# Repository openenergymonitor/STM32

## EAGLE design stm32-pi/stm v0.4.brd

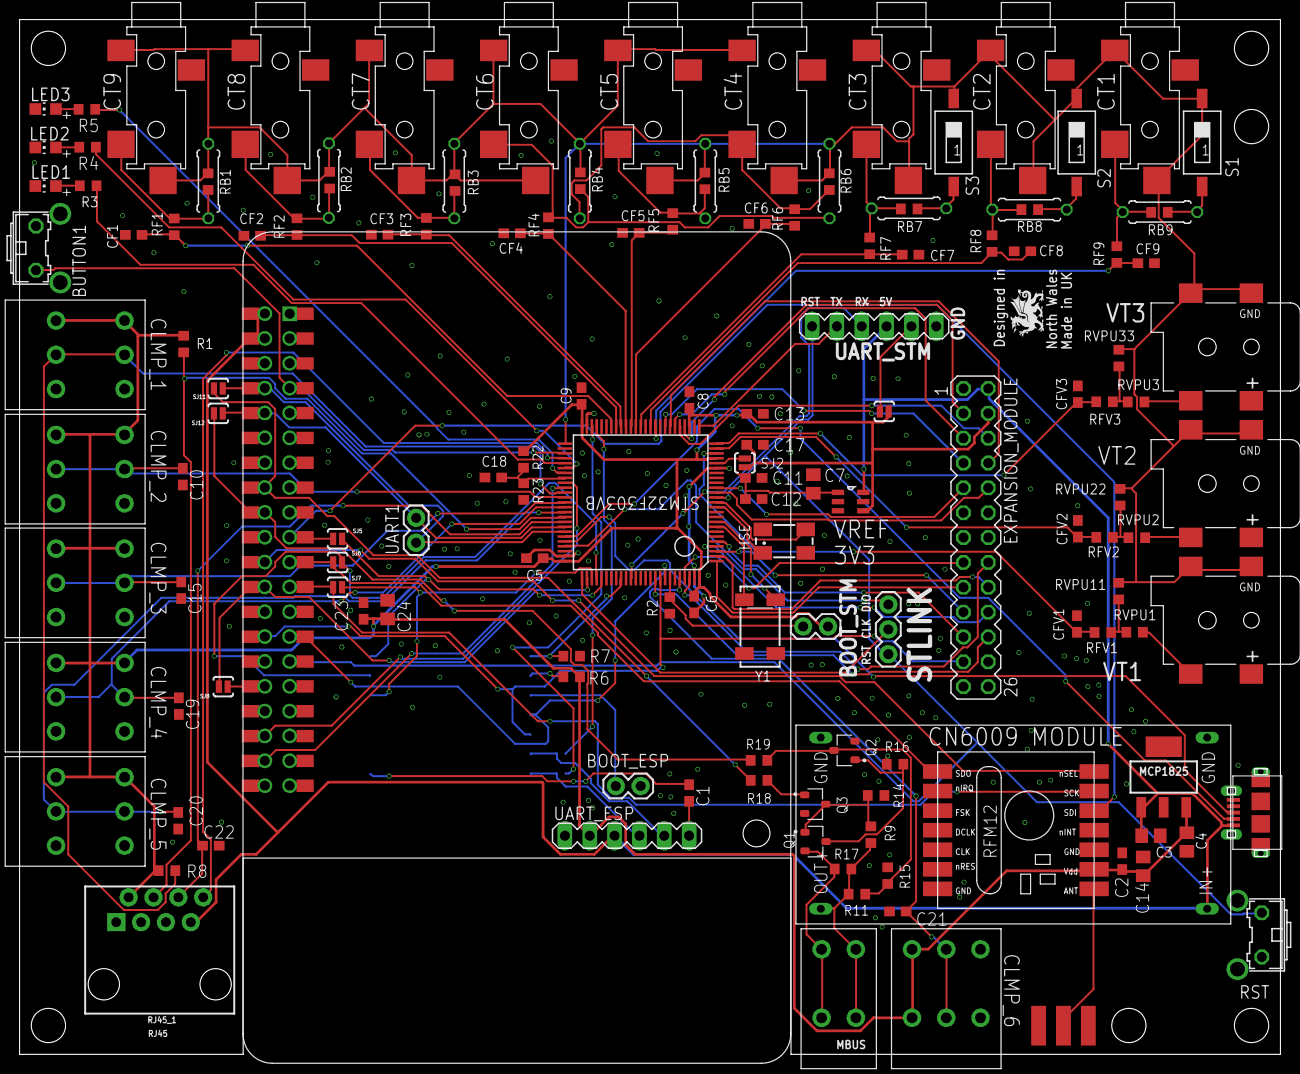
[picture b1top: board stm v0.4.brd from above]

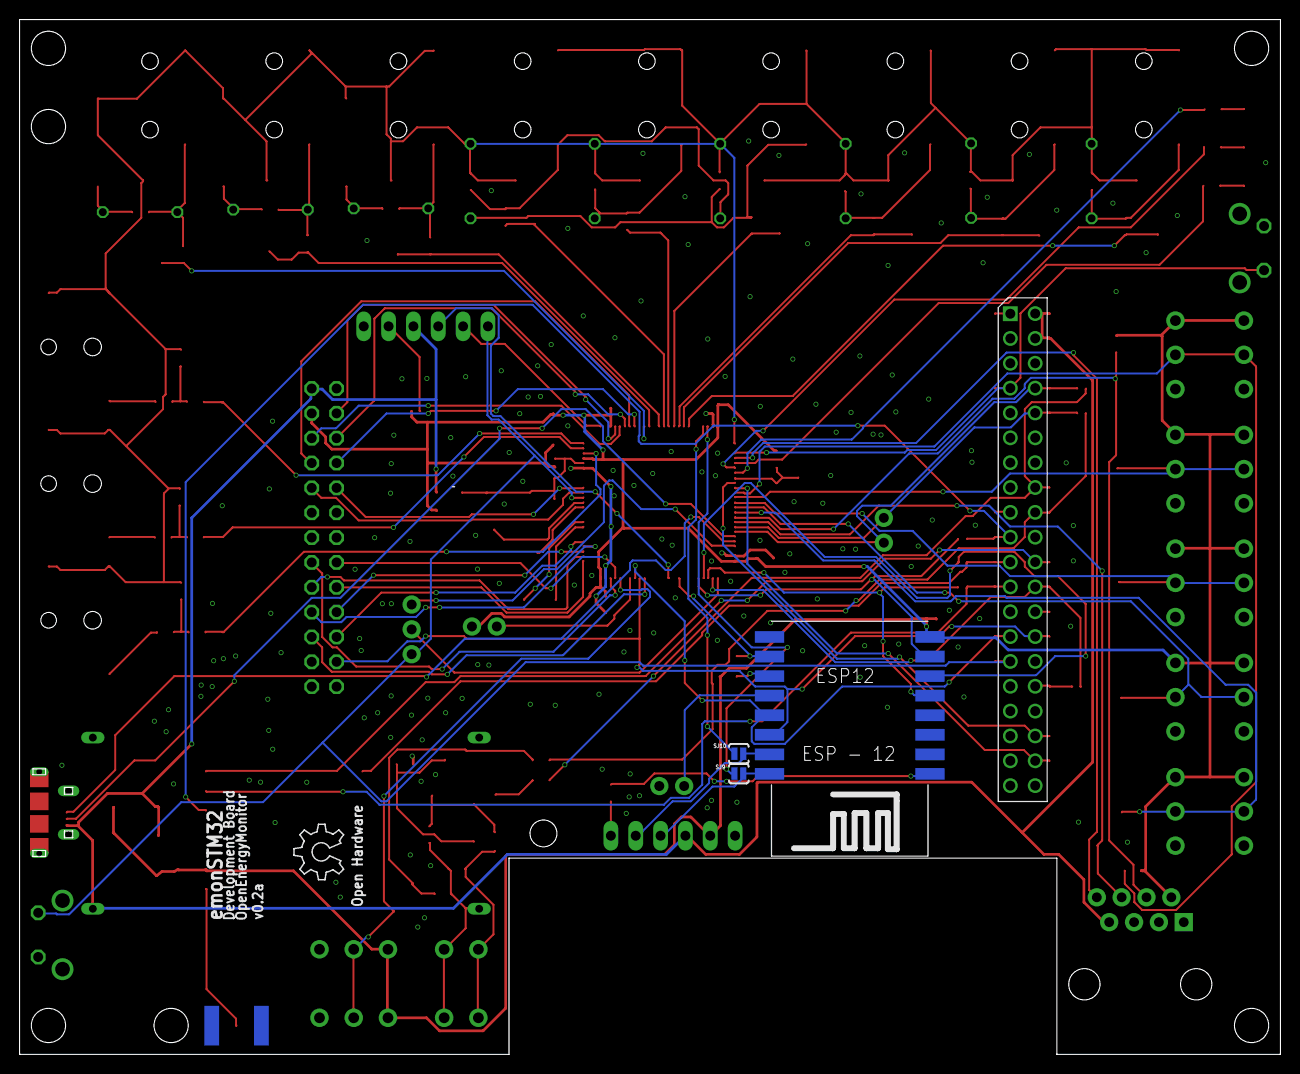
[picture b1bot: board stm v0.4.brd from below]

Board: 2 copper layers, 128.9 x 105.8 mm, 149 parts (4 on the bottom side), 116 nets.

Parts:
2POLE_MBUS: OMNIMATE_LSF_2
3POLE_1, 3POLE_2, 3POLE_3, 3POLE_4, 3POLE_5, 3POLE_6: OMNIMATE_LSF_3
BOOT_ESP: 1X02
BOOT_STM: 1X02
BUTTON1: B3F-31XX
C1, C2, C5, C6, C8, C9, C10, C15, C19, C20, C21, C22, C23: 100nF; C0603
C3, C4: 4.7uF; C0805
C7, C14: 1uF; C0805
C11, C13: 10nF; C0603
C12, C17: 1uF; C0603
C18: 10uF; C0603
C24: 47uF; C0805
CF1, CF2, CF3, CF4, CF5, CF6, CF7, CF8, CF9: 100nF; C0603
CFV1, CFV2, CFV3: 100nF; C0603
CT1, CT2, CT3, CT4, CT5, CT6, CT7, CT8, CT9: STEREO_SMD; STEREO_SMT
ESP12: ESP12-SMD
EXPANSION_MODULE: MA13-2
HSE: 8MHZ ~15pFmax; CTS406
J$1: SMA_EDGE; SMA-EDGE
LED1, LED2, LED3: Red 1.85V; CHIP-LED0805
LOGO1: OSHW_LOGO_6MILX0200-NT; OSHW_6X200_NOTEXT
MCP1825: MCP1825SOT-223-3; SOT-223
PCB2: RPI3YA; RPI3MIRROR2
Q1: MMBT3906; SOT23
Q2, Q3: MMBT3904; SOT23
R1, R8: 4.7k; R0603
R2, R6, R7, R22, R23: 10k; R0603
R3, R4, R5: 220R; R0603
R9: 39K; R0603
R11: 33K; R0603
R14: 22K; R0603
R15: 3k3; R0603
R16: 82R; R0603
R17: 220K; R0603
R18, R19: 1K; R0603
RB1, RB2, RB3, RB4, RB5, RB6, RB7, RB8, RB9: 22r; R0603
RB10, RB11, RB12, RB13, RB14, RB15, RB16, RB17, RB18: 22r; 0207/7
RF1, RF2, RF3, RF4, RF5, RF6, RF7, RF8, RF9: 330R; R0603
RFM69HCW: RFM12_SMDSMD; RFM12
RFV1, RFV2, RFV3: 330R; R0603
RJ45_1: RJ45; RJ45-8
RST: B3F-31XX
RVPU1, RVPU2, RVPU3: 120k; R0603
RVPU11, RVPU22, RVPU33: 10k; R0603
S1, S2, S3: SWS001; SMS-001
SJ1, SJ2, SJ5, SJ6, SJ7, SJ8, SJ9, SJ10, SJ11, SJ12: SOLDERJUMPERNO; SJ_2S-NO
STLINK: 1X03
STM32F303VB: STM32F303XB; TQFP100
U$2: BOOST_MODULE; BOOST
UART1: 1X02
UART_ESP: MA06-1
UART_STM: MA06-1
USB_CONN: MICRO-USB-RECEPTACLE47589-0001; 47589-0001
VREF_3V3: MCP1501T-33E; SOT95P280X145-6N
VT1, VT2, VT3: 2.1MMJACKSMT; DCJACK_2MM_SMT
Y1: 32.768kHz; CRYSTAL_8X3.8

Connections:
24V: 2POLE_MBUS.P$3, 2POLE_MBUS.P$4, R9.2, R11.2, R17.2, U$2.OUT+
+3V3: 3POLE_1.P$1, 3POLE_1.P$2, 3POLE_2.P$1, 3POLE_2.P$2, 3POLE_3.P$1, 3POLE_3.P$2, 3POLE_4.P$1, 3POLE_4.P$2, 3POLE_5.P$1, 3POLE_5.P$2, 3POLE_6.P$1, 3POLE_6.P$2, BOOT_STM.2, C2.1, C4.2, C5.2, C6.2, C8.2, C9.2, C13.1, C14.1, C17.1, C23.1, C24.1, ESP12.VCC, EXPANSION_MODULE.4, MCP1825.3, R1.2, R6.2, R8.2, R22.2, RFM69HCW.9, RJ45_1.2, SJ1.2, SJ2.1, STM32F303VB.22, STM32F303VB.28, STM32F303VB.50, STM32F303VB.75, STM32F303VB.100, UART_ESP.2, VREF_3V3.4
+3V3_ADC: C7.1, C11.1, C12.1, SJ2.2, STM32F303VB.21, VREF_3V3.1
+5V: C3.2, EXPANSION_MODULE.2, MCP1825.1, PCB2.P$2, PCB2.P$4, PCB2.P$42, PCB2.P$44, RJ45_1.7, U$2.IN+, UART_ESP.3, UART_STM.3, USB_CONN.1, VREF_3V3.6
AC1: RVPU1.2, VT1.PWR2
AC2: RVPU2.2, VT2.PWR2
AC3: RVPU3.1, VT3.PWR2
ADC0: RFV3.1, RVPU3.2, RVPU33.1
ADC_RJ45IN: RJ45_1.8, STM32F303VB.54
ANT: J$1.SIG, RFM69HCW.8
BIAS: CT1.P$1, CT1.P$4, CT2.P$1, CT2.P$4, CT3.P$1, CT3.P$4, CT4.P$1, CT4.P$4, CT5.P$1, CT5.P$4, CT6.P$1, CT6.P$4, CT7.P$1, CT7.P$4, CT8.P$1, CT8.P$4, CT9.P$1, CT9.P$4, RB1.2, RB2.2, RB3.2, RB4.2, RB5.2, RB6.2, RB10.2, RB11.2, RB12.2, RB13.2, RB14.2, RB15.2, RVPU11.2, RVPU22.2, RVPU33.2, S1.2, S2.2, S3.2, STM32F303VB.51, VT1.GND, VT1.GNDBREAK, VT2.GND, VT2.GNDBREAK, VT3.GND, VT3.GNDBREAK
BIAS_IN: C18.2, R22.1, R23.2, STM32F303VB.58
BOOT0: BOOT_STM.1, R2.1, STM32F303VB.94
BUTTON1: BUTTON1.2, PCB2.P$7, PCB2.P$47, STM32F303VB.53
CS_RFM69: PCB2.P$22, PCB2.P$62, RFM69HCW.14
CT1: CF1.2, RF1.2, STM32F303VB.44
CT1_EX: EXPANSION_MODULE.3, STM32F303VB.29
CT2: CF2.2, RF2.2, STM32F303VB.43
CT2_EX: EXPANSION_MODULE.6, STM32F303VB.30
CT3: CF3.2, RF3.2, STM32F303VB.42
CT3_EX: EXPANSION_MODULE.5, STM32F303VB.31
CT4: CF4.2, RF4.2, STM32F303VB.41
CT4_EX: EXPANSION_MODULE.8, STM32F303VB.32
CT5: CF5.2, RF5.2, STM32F303VB.40
CT5_EX: EXPANSION_MODULE.7, STM32F303VB.33
CT6: CF6.2, RF6.2, STM32F303VB.39
CT6_EX: EXPANSION_MODULE.10, STM32F303VB.15
CT7: CF7.2, RF7.2, STM32F303VB.38
CT7_EX: EXPANSION_MODULE.9, STM32F303VB.16
CT8: CF8.2, RF8.2, STM32F303VB.36
CT9: CF9.2, RF9.2, STM32F303VB.35
D+: STM32F303VB.71, USB_CONN.3
D-: STM32F303VB.70, USB_CONN.2
DS18B20_2: 3POLE_1.P$3, 3POLE_1.P$4, R8.1, STM32F303VB.61
DS18B20_RJ45: R1.1, RJ45_1.4, STM32F303VB.66
GND: 3POLE_1.P$5, 3POLE_1.P$6, 3POLE_2.P$5, 3POLE_2.P$6, 3POLE_3.P$5, 3POLE_3.P$6, 3POLE_4.P$5, 3POLE_4.P$6, 3POLE_5.P$5, 3POLE_5.P$6, 3POLE_6.P$5, 3POLE_6.P$6, BOOT_ESP.2, BUTTON1.1, C2.2, C3.1, C4.1, C5.1, C6.1, C7.2, C8.1, C9.1, C10.2, C11.2, C12.2, C13.2, C14.2, C15.2, C17.2, C18.1, C19.2, C20.2, C21.2, C22.2, C23.2, C24.2, CF1.1, CF2.1, CF3.1, CF4.1, CF5.1, CF6.1, CF7.1, CF8.1, CF9.1, CFV1.1, CFV2.1, CFV3.1, ESP12.GND, EXPANSION_MODULE.1, EXPANSION_MODULE.14, EXPANSION_MODULE.26, J$1.GND@0, J$1.GND@1, J$1.GND@2, J$1.GND@3, LED1.C, LED2.C, LED3.C, MCP1825.2, MCP1825.4, PCB2.P$6, PCB2.P$9, PCB2.P$14, PCB2.P$20, PCB2.P$25, PCB2.P$30, PCB2.P$34, PCB2.P$39, PCB2.P$46, PCB2.P$49, PCB2.P$54, PCB2.P$60, PCB2.P$65, PCB2.P$70, PCB2.P$74, PCB2.P$79, Q2.2, Q3.2, R2.2, R7.2, R14.1, R15.1, R16.1, R23.1, RFM69HCW.7, RFM69HCW.10, RJ45_1.1, RJ45_1.3, RJ45_1.5, RST.1, STM32F303VB.20, STM32F303VB.49, STM32F303VB.74, STM32F303VB.99, U$2.P$1, U$2.P$2, UART_ESP.1, UART_STM.1, USB_CONN.5, USB_CONN.CASING1, USB_CONN.CASING2, USB_CONN.CASING3, USB_CONN.CASING4, VREF_3V3.2, VREF_3V3.3, VREF_3V3.5
HSE_IN: HSE.1, STM32F303VB.12
HSE_OUT: HSE.3, STM32F303VB.13
IO1_EX: EXPANSION_MODULE.15, STM32F303VB.97
IO2_EX: EXPANSION_MODULE.16, STM32F303VB.98
IO3_EX: EXPANSION_MODULE.17, STM32F303VB.1
IO4_EX: EXPANSION_MODULE.18, STM32F303VB.2
IO5_EX: EXPANSION_MODULE.19, STM32F303VB.3
IO6_EX: EXPANSION_MODULE.20, STM32F303VB.4
IO7_EX: EXPANSION_MODULE.21, STM32F303VB.5
IO8_EX: EXPANSION_MODULE.22, STM32F303VB.91
LED1: R3.2, STM32F303VB.55
LED2: R4.2, STM32F303VB.56
LED3: R5.2, STM32F303VB.57
MBUS_RX: PCB2.P$16, PCB2.P$56, R18.2, SJ11.2
MBUS_TX: PCB2.P$18, PCB2.P$58, R19.2, SJ12.2
MISO: PCB2.P$21, PCB2.P$61, RFM69HCW.1, SJ6.2
MOSI: PCB2.P$19, PCB2.P$59, RFM69HCW.12, SJ5.2
unnamed: SJ1.1, UART_STM.2
unnamed: CT9.P$2, RB1.1, RB10.1, RF1.1
unnamed: LED2.A, R4.1
unnamed: LED3.A, R5.1
unnamed: BOOT_ESP.1, ESP12.GPIO0
unnamed: CT8.P$2, RB2.1, RB11.1, RF2.1
unnamed: CT7.P$2, RB3.1, RB12.1, RF3.1
unnamed: ESP12.GPIO2, R6.1
unnamed: PCB2.P$26, PCB2.P$66
unnamed: PCB2.P$32, PCB2.P$72, SJ8.1
unnamed: PCB2.P$1, PCB2.P$41
unnamed: PCB2.P$17, PCB2.P$57
unnamed: RB9.2, RB18.2, S1.1
unnamed: RB8.2, RB17.2, S2.1
unnamed: RB7.2, RB16.2, S3.1
unnamed: 2POLE_MBUS.P$1, 2POLE_MBUS.P$2, Q1.2, R17.1
unnamed: Q1.3, Q2.1, R16.2
unnamed: Q1.1, Q3.3, R9.1, R14.2
unnamed: Q2.3, R11.1, R15.2, R19.1
unnamed: Q3.1, R18.1
unnamed: RFV2.1, RVPU2.1, RVPU22.1
unnamed: RFV1.1, RVPU1.1, RVPU11.1
unnamed: CT6.P$2, RB4.1, RB15.1, RF4.1
unnamed: CT5.P$2, RB5.1, RB14.1, RF5.1
unnamed: CT4.P$2, RB6.1, RB13.1, RF6.1
unnamed: LED1.A, R3.1
unnamed: CT3.P$2, RB7.1, RB16.1, RF7.1
unnamed: CT2.P$2, RB8.1, RB17.1, RF8.1
unnamed: CT1.P$2, RB9.1, RB18.1, RF9.1
NRST: PCB2.P$29, PCB2.P$69, RST.2, STLINK.3, STM32F303VB.14, UART_STM.6
PC14: STM32F303VB.8, Y1.P$1
PC15: STM32F303VB.9, Y1.P$4
PULSE1_RJ45: C22.1, RJ45_1.6, STM32F303VB.67
PULSE2: 3POLE_5.P$3, 3POLE_5.P$4, C20.1, STM32F303VB.65
PUSHIN_1: 3POLE_6.P$3, 3POLE_6.P$4, C21.1, STM32F303VB.96
PUSHIN_2: 3POLE_2.P$3, 3POLE_2.P$4, C10.1, STM32F303VB.62
PUSHIN_3: 3POLE_3.P$3, 3POLE_3.P$4, C15.1, STM32F303VB.63
PUSHIN_4: 3POLE_4.P$3, 3POLE_4.P$4, C19.1, STM32F303VB.64
RPI_GPIO16: PCB2.P$36, PCB2.P$76, STM32F303VB.59
RPI_GPIO20: PCB2.P$38, PCB2.P$78, STM32F303VB.60
RST_ESP_1: C1.2, UART_ESP.6
RST_ESP_2: C1.1, ESP12.RESET
SCK: ESP12.GPIO5, EXPANSION_MODULE.23, PCB2.P$28, PCB2.P$68, STM32F303VB.92
SDA: ESP12.GPIO4, PCB2.P$27, PCB2.P$67, STM32F303VB.93
SPI3_CLK: ESP12.GPIO14, SJ7.1, STM32F303VB.78
SPI3_CS: PCB2.P$24, PCB2.P$64, SJ8.2, STM32F303VB.77
SPI3_CS_ESP: ESP12.GPIO15, R7.1, STM32F303VB.84
SPI3_MISO: ESP12.GPIO12, SJ6.1, STM32F303VB.79
SPI3_MOSI: ESP12.GPIO13, SJ5.1, STM32F303VB.80
SPI_CLK: PCB2.P$23, PCB2.P$63, RFM69HCW.13, SJ7.2
SWCLK: STLINK.2, STM32F303VB.76
SWDIO: STLINK.1, STM32F303VB.72
UART1_RX: PCB2.P$8, PCB2.P$48, SJ11.1, STM32F303VB.69, UART1.1
UART1_TX: PCB2.P$10, PCB2.P$50, SJ12.1, STM32F303VB.68, UART1.2
UART_RX: STM32F303VB.86, UART_STM.4
UART_RX_ESP: ESP12.TXD0, SJ9.2, UART_ESP.4
UART_TX: STM32F303VB.26, UART_STM.5
UART_TX_ESP: ESP12.RXD0, SJ10.1, UART_ESP.5
USART3_RX: SJ9.1, STM32F303VB.48
USART3_TX: SJ10.2, STM32F303VB.47
VSIG1: CFV1.2, RFV1.2, STM32F303VB.23
VSIG2: CFV2.2, RFV2.2, STM32F303VB.24
VSIG3: CFV3.2, RFV3.2, STM32F303VB.25

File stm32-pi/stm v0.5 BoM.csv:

Qty,Value,Device,Package,Schematic Reference,Description,CREATED_BY,DIGIKEY_PART_NUMBER,MANUFACTURER,MF,MPN,OC_FARNELL,OC_NEWARK,PACKAGE,PROD_ID,SF_ID,SPICEPREFIX,VALUE
2,,31-XX,B3F-31XX,"BUTTON1, RST",OMRON SWITCH,,,,,B3F-3100,959704,36M3582,,,,,
1,,ESP12SMD,ESP12-SMD,ESP12,ESP8266 Wifi module 12,,,,,,,,,,,,
3,,M02PTH,1X02,"BOOT_ESP, BOOT_STM, UART1",Header 2,,,,,,,,,,,,
1,,M03PTH,1X03,STLINK,Header 3,,,,,,,,,,,,
2,,MA06-1,MA06-1,"UART_ESP, UART_STM",PIN HEADER,,,,,,unknown,unknown,,,,,
1,,MA13-2,MA13-2,EXPANSION_MODULE,PIN HEADER,,,,,,unknown,unknown,,,,,
25,100nF,C-EUC0603,C0603,"C1, C2, C5, C6, C8, C9, C10, C15, C19, C20, C21, C22, C23, CF1, CF2, CF3, CF4, CF5, CF6, CF7, CF8, CF9, CFV1, CFV2, CFV3","CAPACITOR, European symbol",,,,,,,,,,,,
8,10k,R-EU_R0603,R0603,"R2, R6, R7, R22, R23, RVPU11, RVPU22, RVPU33","RESISTOR, European symbol",,,,,,,,,,,,
2,10nF,C-EUC0603,C0603,"C11, C13","CAPACITOR, European symbol",,,,,,,,,,,C,
1,10uF,C-EUC0603,C0603,C18,"CAPACITOR, European symbol",,,,,,,,,,,,
3,120k,R-EU_R0603,R0603,"RVPU1, RVPU2, RVPU3","RESISTOR, European symbol",,,,,,,,,,,,
2,1K,R-EU_R0603,R0603,"R18, R19","RESISTOR, European symbol",,,,,,,,,,,R,
2,1uF,C-EUC0603,C0603,"C12, C17","CAPACITOR, European symbol",,,,,,,,,,,,
2,1uF,C-EUC0805,C0805,"C7, C14","CAPACITOR, European symbol",,,,,,,,,,,C,
3,2.1MMJACKSMT,2.1MMJACKSMT,DCJACK_2MM_SMT,"VT1, VT2, VT3","2.1mm x 5.5mm THM DC jack with internal switch. Digikey part #PJ-102A, 4UCON part #05537",,,,,,,,,,,,
1,220K,R-EU_R0603,R0603,R17,"RESISTOR, European symbol",,,,,,,,,,,R,
3,220R,R-EU_R0603,R0603,"R3, R4, R5","RESISTOR, European symbol",,,,,,,,,,,R,
1,22K,R-EU_R0603,R0603,R14,"RESISTOR, European symbol",,,,,,,,,,,R,
9,22r,R-EU_0207/7,0207/7,"RB10, RB11, RB12, RB13, RB14, RB15, RB16, RB17, RB18","RESISTOR, European symbol",,,,,,,,,,,R,
9,22r,R-EU_R0603,R0603,"RB1, RB2, RB3, RB4, RB5, RB6, RB7, RB8, RB9","RESISTOR, European symbol",,,,,,,,,,,,
1,32.768kHz,CRYSTAL8X3.8SMT,CRYSTAL_8X3.8,Y1,Crystals,,,,,,,,,,,,
12,330R,R-EU_R0603,R0603,"RF1, RF2, RF3, RF4, RF5, RF6, RF7, RF8, RF9, RFV1, RFV2, RFV3","RESISTOR, European symbol",,,,,,,,,,,,
1,33K,R-EU_R0603,R0603,R11,"RESISTOR, European symbol",,,,,,,,,,,R,
1,39K,R-EU_R0603,R0603,R9,"RESISTOR, European symbol",,,,,,,,,,,R,
1,3k3,R-EU_R0603,R0603,R15,"RESISTOR, European symbol",,,,,,,,,,,R,
2,4.7k,R-EU_R0603,R0603,"R1, R8","RESISTOR, European symbol",,,,,,,,,,,,
2,4.7uF,C-EUC0805,C0805,"C3, C4","CAPACITOR, European symbol",,,,,,,,,,,C,
1,47uF,C-EUC0805,C0805,C24,"CAPACITOR, European symbol",,,,,,,,,,,C,
1,82R,R-EU_R0603,R0603,R16,"RESISTOR, European symbol",,,,,,,,,,,R,
1,8MHZ ~15pFmax,CRYSTALCTS406,CTS406,HSE,CRYSTAL,,,,,,unknown,unknown,,,,,
1,BOOST_MODULE,BOOST_MODULE,BOOST,U$2,,,,,,,,,,,,,
1,MCP1501T-33E,MCP1501T-33E,SOT95P280X145-6N,VREF_3V3,,,,,,,,,,,,,
1,MCP1825SOT-223-3,MCP1825SOT-223-3,SOT-223,MCP1825,MCP1825 3.3v LDO Linear Regulator,,,,,,,,,,,,
1,MICRO-USB-RECEPTACLE47589-0001,MICRO-USB-RECEPTACLE47589-0001,47589-0001,USB_CONN,MICRO USB RECEPTACLES,,,,,,,,,,,,
2,MMBT3904,MMBT3904,SOT23,"Q2, Q3",TRANS NPN 40V 0.2A SOT-23,PCB Layout,MMBT3904FSCT-ND,ON Semiconductor,,MMBT3904,,,SOT-23-3,,,,
1,MMBT3906,MMBT3906,SOT23,Q1,TRANS PNP 40V 0.2A SOT-23,PCB Layout,MMBT3906FSCT-ND,ON Semiconductor,,MMBT3906,,,SOT-23,,,,
1,OMNIMATE_LSF_2,OMNIMATE_LSF_2,OMNIMATE_LSF_2,2POLE_MBUS,,,,,,,,,,,,,
6,OMNIMATE_LSF_3,OMNIMATE_LSF_3,OMNIMATE_LSF_3,"3POLE_1, 3POLE_2, 3POLE_3, 3POLE_4, 3POLE_5, 3POLE_6",,,,,,,,,,,,,
1,RFM12_SMDSMD,RFM12_SMDSMD,RFM12,RFM69HCW,RFM12 is a low costing ISM band transceiver,,,,,,,,,,,,
1,RJ45,RJ45-8,RJ45-8,RJ45_1,RJ45 Jack - 8 pin,,,,,,,,,CONN-08506,PRT-00643,,RJ45
1,RPI3YA,RPI3YA,RPI3MIRROR2,PCB2,Device for Raspberry Pi 3 board created by Dave Young for www.element14.com,,,,,,,,,,,,
3,Red 1.85V,LEDCHIP-LED0805,CHIP-LED0805,"LED1, LED2, LED3",LED,,,,,,,,,,,,
1,SMA_EDGE,SMA_EDGE,SMA-EDGE,J$1,SMA Antenna Connector,,,,,,,,,,,,
10,SOLDERJUMPERNO,SOLDERJUMPERNO,SJ_2S-NO,"SJ1, SJ2, SJ5, SJ6, SJ7, SJ8, SJ9, SJ10, SJ11, SJ12",Solder Jumper,,,,,,,,,,,,
9,STEREO_SMD,STEREO_SMD,STEREO_SMT,"CT1, CT2, CT3, CT4, CT5, CT6, CT7, CT8, CT9",3.5mm Stereo Jack SMT,,,,,SJ-3524-SMT-TR ,,,,,,,
1,STM32F303XB,STM32F303XB,TQFP100,STM32F303VB STM32F303VD STM32F303VE (flash size),,,,,,STM32F303VBT6TR ,,,,,,,
3,SWS001,SWS001,SMS-001,"S1, S2, S3",SMD Dip Switch 1 pol.,,,,,,,,,,,,

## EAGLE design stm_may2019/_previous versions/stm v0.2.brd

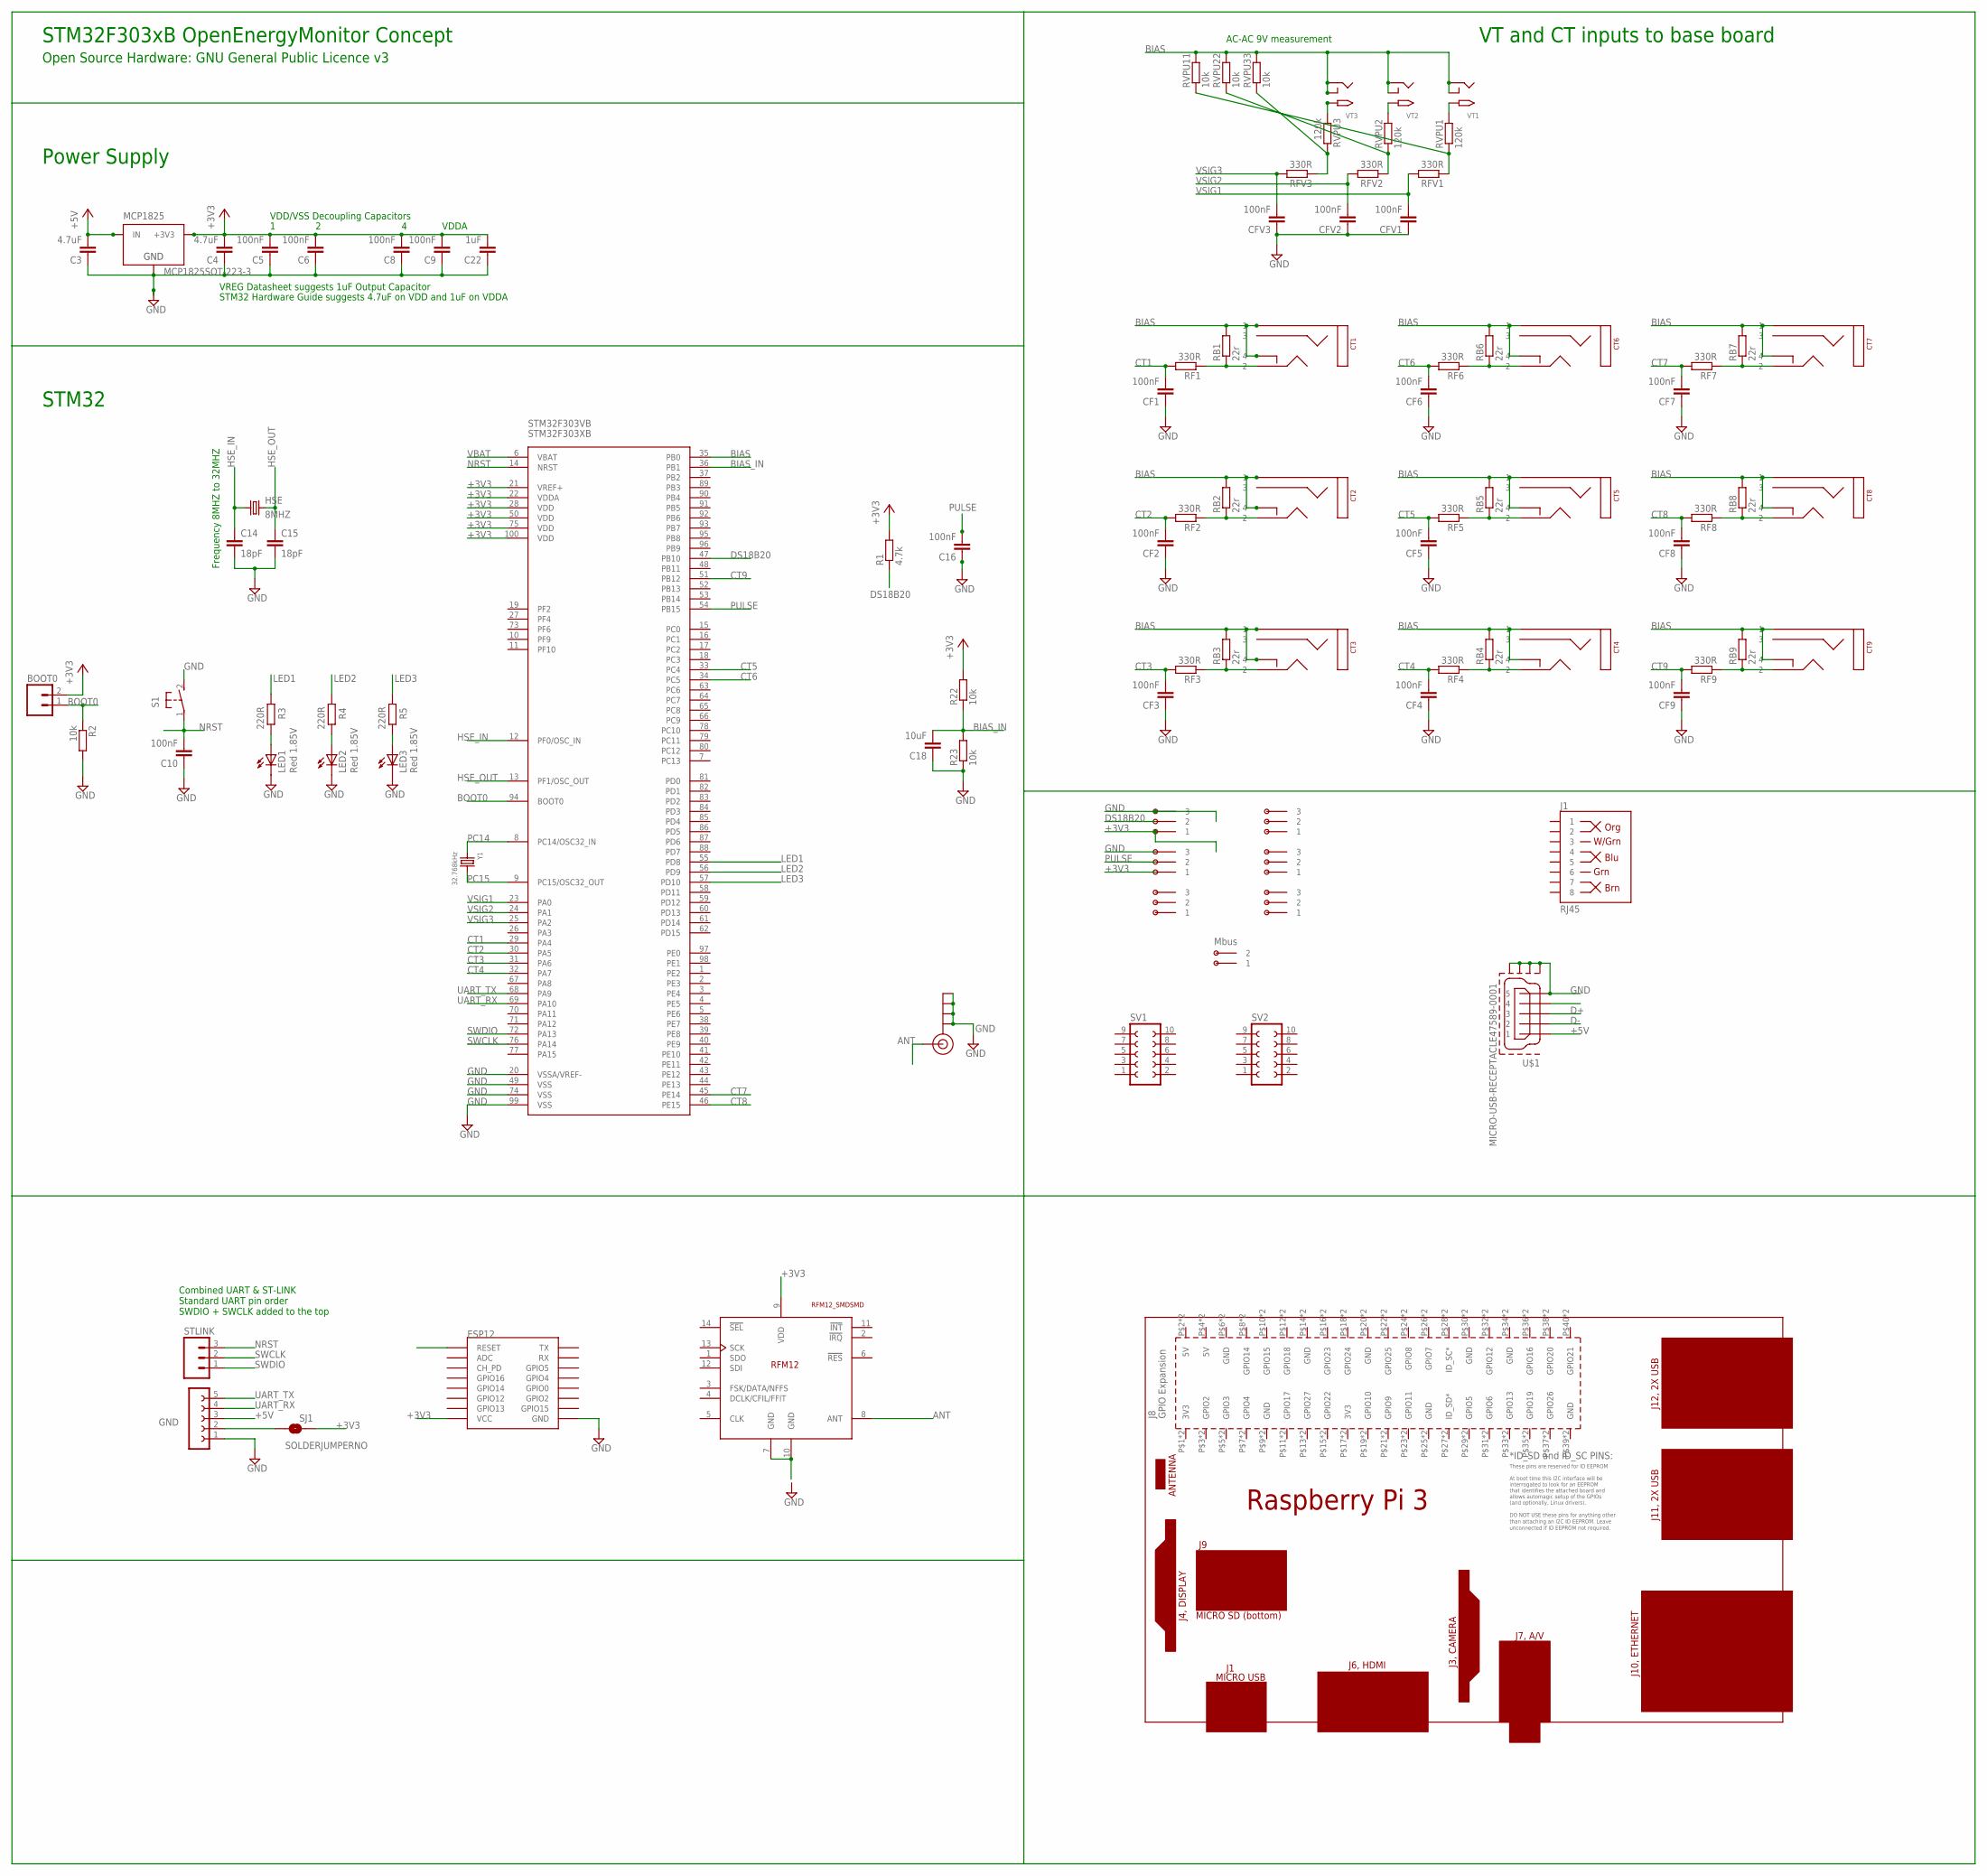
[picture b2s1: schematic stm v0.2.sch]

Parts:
BOOT0: M02PTH; 1X02
C3, C4: 4.7uF; C1210
C5, C6, C8, C9, C10, C16: 100nF; C0603
C14, C15: 18pF; C0603
C18: 10uF; C0603
C22: 1uF; C1210
CF1, CF2, CF3, CF4, CF5, CF6, CF7, CF8, CF9: 100nF; C0603
CFV1, CFV2, CFV3: 100nF; C0603
CT1, CT2, CT3, CT4, CT5, CT6, CT7, CT8, CT9: STEREO_SMD; STEREO_SMT
ESP12: ESP12SMD; ESP12-SMD
GND: UART; FE05-1
HSE: 8MHZ; CTS406
J1: RJ45; RJ45-8
J$1: SMA_EDGE; SMA-EDGE
LED1, LED2, LED3: Red 1.85V; CHIP-LED0805
MCP1825: MCP1825SOT-223-3; SOT-223
PCB2: RPI3YA; RPI3MIRROR2
R1: 4.7k; R0603
R2, R22, R23: 10k; R0603
R3, R4, R5: 220R; R0603
RB1, RB2, RB3, RB4, RB5, RB6, RB7, RB8, RB9: 22r; R0603
RF1, RF2, RF3, RF4, RF5, RF6, RF7, RF8, RF9: 330R; R0603
RFM69HCW: RFM12_SMDSMD; RFM12
RFV1, RFV2, RFV3: 330R; R0603
RVPU1, RVPU2, RVPU3: 120k; R0603
RVPU11, RVPU22, RVPU33: 10k; R0603
S1: 31-XX; B3F-31XX
SJ1: SOLDERJUMPERNO; SJ_2S-NO
STLINK: M03PTH; 1X03
STM32F303VB: STM32F303XB; TQFP100
SV1, SV2: FE05-2
U$1: MICRO-USB-RECEPTACLE47589-0001; 47589-0001
U$2, U$3, U$4, U$5, U$6, U$7: OMNIMATE_LSF_3
U$11: OMNIMATE_LSF_2
VT1, VT2, VT3: 2.1MMJACKSMT; DCJACK_2MM_SMT
Y1: 32.768kHz; CRYSTAL_8X3.8

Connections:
+3V3: BOOT0.2, C4.2, C5.2, C6.2, C8.2, C9.2, C22.2, ESP12.VCC, MCP1825.3 (+3V3), R1.2, R22.2, RFM69HCW.9 (VDD), SJ1.2, STM32F303VB.21 (VREF+), STM32F303VB.22 (VDDA), STM32F303VB.28 (VDD), STM32F303VB.50 (VDD), STM32F303VB.75 (VDD), STM32F303VB.100 (VDD), U$4.P$1 (1), U$4.P$2 (1), U$5.P$1 (1), U$5.P$2 (1)
+5V: C3.2, GND.3, MCP1825.1 (IN), U$1.1
AC1: RVPU1.2, VT1.PWR2 (TIP)
AC2: RVPU2.2, VT2.PWR2 (TIP)
AC3: RVPU3.1, VT3.PWR2 (TIP)
ADC0: RFV3.1, RVPU3.2, RVPU33.1
ANT: J$1.SIG (SIGNAL), RFM69HCW.8 (ANT)
BIAS: CT1.P$1 (1), CT1.P$4 (4), CT2.P$1 (1), CT2.P$4 (4), CT3.P$1 (1), CT3.P$4 (4), CT4.P$1 (1), CT4.P$4 (4), CT5.P$1 (1), CT5.P$4 (4), CT6.P$1 (1), CT6.P$4 (4), CT7.P$1 (1), CT7.P$4 (4), CT8.P$1 (1), CT8.P$4 (4), CT9.P$1 (1), CT9.P$4 (4), RB1.2, RB2.2, RB3.2, RB4.2, RB5.2, RB6.2, RB7.2, RB8.2, RB9.2, RVPU11.2, RVPU22.2, RVPU33.2, STM32F303VB.35 (PB0), VT1.GND (RING), VT1.GNDBREAK (RING_SW), VT2.GND (RING), VT2.GNDBREAK (RING_SW), VT3.GND (RING), VT3.GNDBREAK (RING_SW)
BIAS_IN: C18.2, R22.1, R23.2, STM32F303VB.36 (PB1)
BOOT0: BOOT0.1, R2.1, STM32F303VB.94 (BOOT0)
CT1: CF1.2, RF1.2, STM32F303VB.29 (PA4)
CT2: CF2.2, RF2.2, STM32F303VB.30 (PA5)
CT3: CF3.2, RF3.2, STM32F303VB.31 (PA6)
CT4: CF4.2, RF4.2, STM32F303VB.32 (PA7)
CT5: CF5.2, RF5.2, STM32F303VB.33 (PC4)
CT6: CF6.2, RF6.2, STM32F303VB.34 (PC5)
CT7: CF7.2, RF7.2, STM32F303VB.45 (PE14)
CT8: CF8.2, RF8.2, STM32F303VB.46 (PE15)
CT9: CF9.2, RF9.2, STM32F303VB.51 (PB12)
D+: U$1.3
D-: U$1.2
DS18B20: R1.1, STM32F303VB.47 (PB10), U$4.P$3 (2), U$4.P$4 (2)
GND: C3.1, C4.1, C5.1, C6.1, C8.1, C9.1, C10.1, C14.2, C15.2, C16.1, C18.1, C22.1, CF1.1, CF2.1, CF3.1, CF4.1, CF5.1, CF6.1, CF7.1, CF8.1, CF9.1, CFV1.1, CFV2.1, CFV3.1, ESP12.GND, GND.1, J$1.GND@0 (GND), J$1.GND@1 (GND), J$1.GND@2 (GND), J$1.GND@3 (GND), LED1.C, LED2.C, LED3.C, MCP1825.2 (GND), R2.2, R23.1, S1.2 (S), STM32F303VB.20 (VSSA/VREF-), STM32F303VB.49 (VSS), STM32F303VB.74 (VSS), STM32F303VB.99 (VSS), U$1.5, U$1.CASING1 (GND1), U$1.CASING2 (GND2), U$1.CASING3 (GND3), U$1.CASING4 (GND4), U$4.P$5 (3), U$4.P$6 (3), U$5.P$5 (3), U$5.P$6 (3)
HSE_IN: C14.1, HSE.1, STM32F303VB.12 (PF0/OSC_IN)
HSE_OUT: C15.1, HSE.3 (2), STM32F303VB.13 (PF1/OSC_OUT)
LED1: R3.2, STM32F303VB.55 (PD8)
LED2: R4.2, STM32F303VB.56 (PD9)
LED3: R5.2, STM32F303VB.57 (PD10)
unnamed: GND.2, SJ1.1
unnamed: CT1.P$2 (2), RB1.1, RF1.1
unnamed: LED2.A, R4.1
unnamed: LED3.A, R5.1
unnamed: CT2.P$2 (2), RB2.1, RF2.1
unnamed: RFM69HCW.7 (GND), RFM69HCW.10 (GND)
unnamed: CT3.P$2 (2), RB3.1, RF3.1
unnamed: RFV2.1, RVPU2.1, RVPU22.1
unnamed: RFV1.1, RVPU1.1, RVPU11.1
unnamed: CT4.P$2 (2), RB4.1, RF4.1
unnamed: CT5.P$2 (2), RB5.1, RF5.1
unnamed: CT6.P$2 (2), RB6.1, RF6.1
unnamed: LED1.A, R3.1
unnamed: CT7.P$2 (2), RB7.1, RF7.1
unnamed: CT8.P$2 (2), RB8.1, RF8.1
unnamed: CT9.P$2 (2), RB9.1, RF9.1
NRST: C10.2, S1.1, STLINK.3, STM32F303VB.14 (NRST)
PC14: STM32F303VB.8 (PC14/OSC32_IN), Y1.P$1 (1)
PC15: STM32F303VB.9 (PC15/OSC32_OUT), Y1.P$4 (2)
PULSE: C16.2, STM32F303VB.54 (PB15), U$5.P$3 (2), U$5.P$4 (2)
SWCLK: STLINK.2, STM32F303VB.76 (PA14)
SWDIO: STLINK.1, STM32F303VB.72 (PA13)
UART_RX: GND.4, STM32F303VB.69 (PA10)
UART_TX: GND.5, STM32F303VB.68 (PA9)
VBAT: STM32F303VB.6 (VBAT)
VSIG1: CFV1.2, RFV1.2, STM32F303VB.23 (PA0)
VSIG2: CFV2.2, RFV2.2, STM32F303VB.24 (PA1)
VSIG3: CFV3.2, RFV3.2, STM32F303VB.25 (PA2)

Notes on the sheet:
VDD/VSS Decoupling Capacitors
VDDA
VREG Datasheet suggests 1uF Output Capacitor
STM32 Hardware Guide suggests 4.7uF on VDD and 1uF on VDDA
Combined UART & ST-LINK Standard UART pin order SWDIO + SWCLK added to the top
AC-AC 9V measurement
VT and CT inputs to base board
STM32F303xB OpenEnergyMonitor Concept
Power Supply
STM32
Open Source Hardware: GNU General Public Licence v3
Frequency 8MHZ to 32MHZ
Mbus

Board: 2 copper layers, 98 parts (0 on the bottom side), 53 nets, no tracks yet.

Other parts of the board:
LOGO1: OSHW_LOGO_6MILX0200-NT; OSHW_6X200_NOTEXT

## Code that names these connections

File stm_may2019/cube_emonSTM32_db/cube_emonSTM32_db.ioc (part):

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Mcu.Name=STM32F303V(B-C)Tx
Mcu.Package=LQFP100
Mcu.UserName=STM32F303VCTx
PA0.Mode=IN1-Single-Ended
PA0.Signal=ADC1_IN1
PA1.Mode=IN2-Single-Ended
PA1.Signal=ADC1_IN2
PA10.Mode=Asynchronous
PA10.Signal=USART1_RX
PA13.Signal=SYS_JTMS-SWDIO
PA14.Signal=SYS_JTCK-SWCLK
PA15.Mode=NSS_Signal_Hard_Output
PA15.Signal=SPI3_NSS
PA2.Mode=IN3-Differential
PA2.Signal=ADC1_IN3
PA3.Mode=IN3-Differential
PA3.Signal=ADC1_IN4
PA4.Mode=IN1-Single-Ended
PA4.Signal=ADC2_IN1
PA5.Mode=IN2-Single-Ended
PA5.Signal=ADC2_IN2
PA6.Mode=IN3-Single-Ended
PA6.Signal=ADC2_IN3
PA7.Mode=IN4-Single-Ended
PA7.Signal=ADC2_IN4
PA9.Mode=Asynchronous
PA9.Signal=USART1_TX
PB0.Mode=Follower
PB0.Signal=OPAMP3_VINP
PB1.Mode=Follower
PB1.Signal=OPAMP3_VOUT
PB10.Mode=Asynchronous
PB10.Signal=USART3_TX
PB11.Mode=Asynchronous
PB11.Signal=USART3_RX
PB12.Mode=IN3-Single-Ended
PB12.Signal=ADC4_IN3
PB13.Signal=GPIO_Input
PB15.Signal=GPIO_Input
PC0.Signal=ADCx_IN6
PC1.Signal=ADCx_IN7
PC10.Mode=Full_Duplex_Master
PC10.Signal=SPI3_SCK
PC11.Mode=Full_Duplex_Master
PC11.Signal=SPI3_MISO
PC12.Mode=Full_Duplex_Master
PC12.Signal=SPI3_MOSI
PC2.Signal=ADCx_IN8
PC3.Signal=ADCx_IN9
PC4.Mode=IN5-Single-Ended
PC4.Signal=ADC2_IN5
PC5.Mode=IN11-Single-Ended
PC5.Signal=ADC2_IN11
PD0.Signal=GPIO_Input
PD1.Signal=GPIO_Input
PD10.Signal=GPIO_Output
PD2.Signal=GPIO_Input
PD3.Signal=GPIO_Input
PD8.Signal=GPIO_Output
PD9.Signal=GPIO_Output
PE0.Signal=GPIO_Input
PE1.Signal=GPIO_Input
PE10.Mode=IN14-Single-Ended
PE10.Signal=ADC3_IN14
PE11.Mode=IN15-Single-Ended
PE11.Signal=ADC3_IN15
PE12.Mode=IN16-Single-Ended
PE12.Signal=ADC3_IN16
PE14.Mode=IN1-Single-Ended
PE14.Signal=ADC4_IN1
PE15.Mode=IN2-Single-Ended
PE15.Signal=ADC4_IN2
PE2.Signal=GPIO_Input
PE3.Signal=GPIO_Input
PE7.Mode=IN13-Single-Ended
PE7.Signal=ADC3_IN13
PE8.Signal=ADCx_IN6P
PE9.Mode=IN2-Single-Ended
PE9.Signal=ADC3_IN2
RCC.HSEPLLFreq_Value=8000000
RCC.HSE_VALUE=8000000
RCC.SYSCLKFreq_VALUE=8000000
board=custom

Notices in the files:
parts and their libraries:
SparkFun-Connectors: Licensing: Creative Commons ShareAlike 4.0 International - https://creativecommons.org/licenses/by-sa/4.0
microbuilder: This work is placed in the public domain, and may be freely used for commercial and non-commercial work with the following conditions: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
